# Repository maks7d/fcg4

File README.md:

This project aims to develop an ultra minimalist flight controller for betaflight firmware for FPV drones.
The components are : 
- STM32G473CEU6 (mcu)
- SPL006 (barometer)
- ICM-42688-P (gyro/accel)
No analog OSD and no BlackBox

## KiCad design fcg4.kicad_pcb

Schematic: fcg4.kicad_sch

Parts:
H1: MountingHole; MountingHoles_30.5x30.5mm_Standard

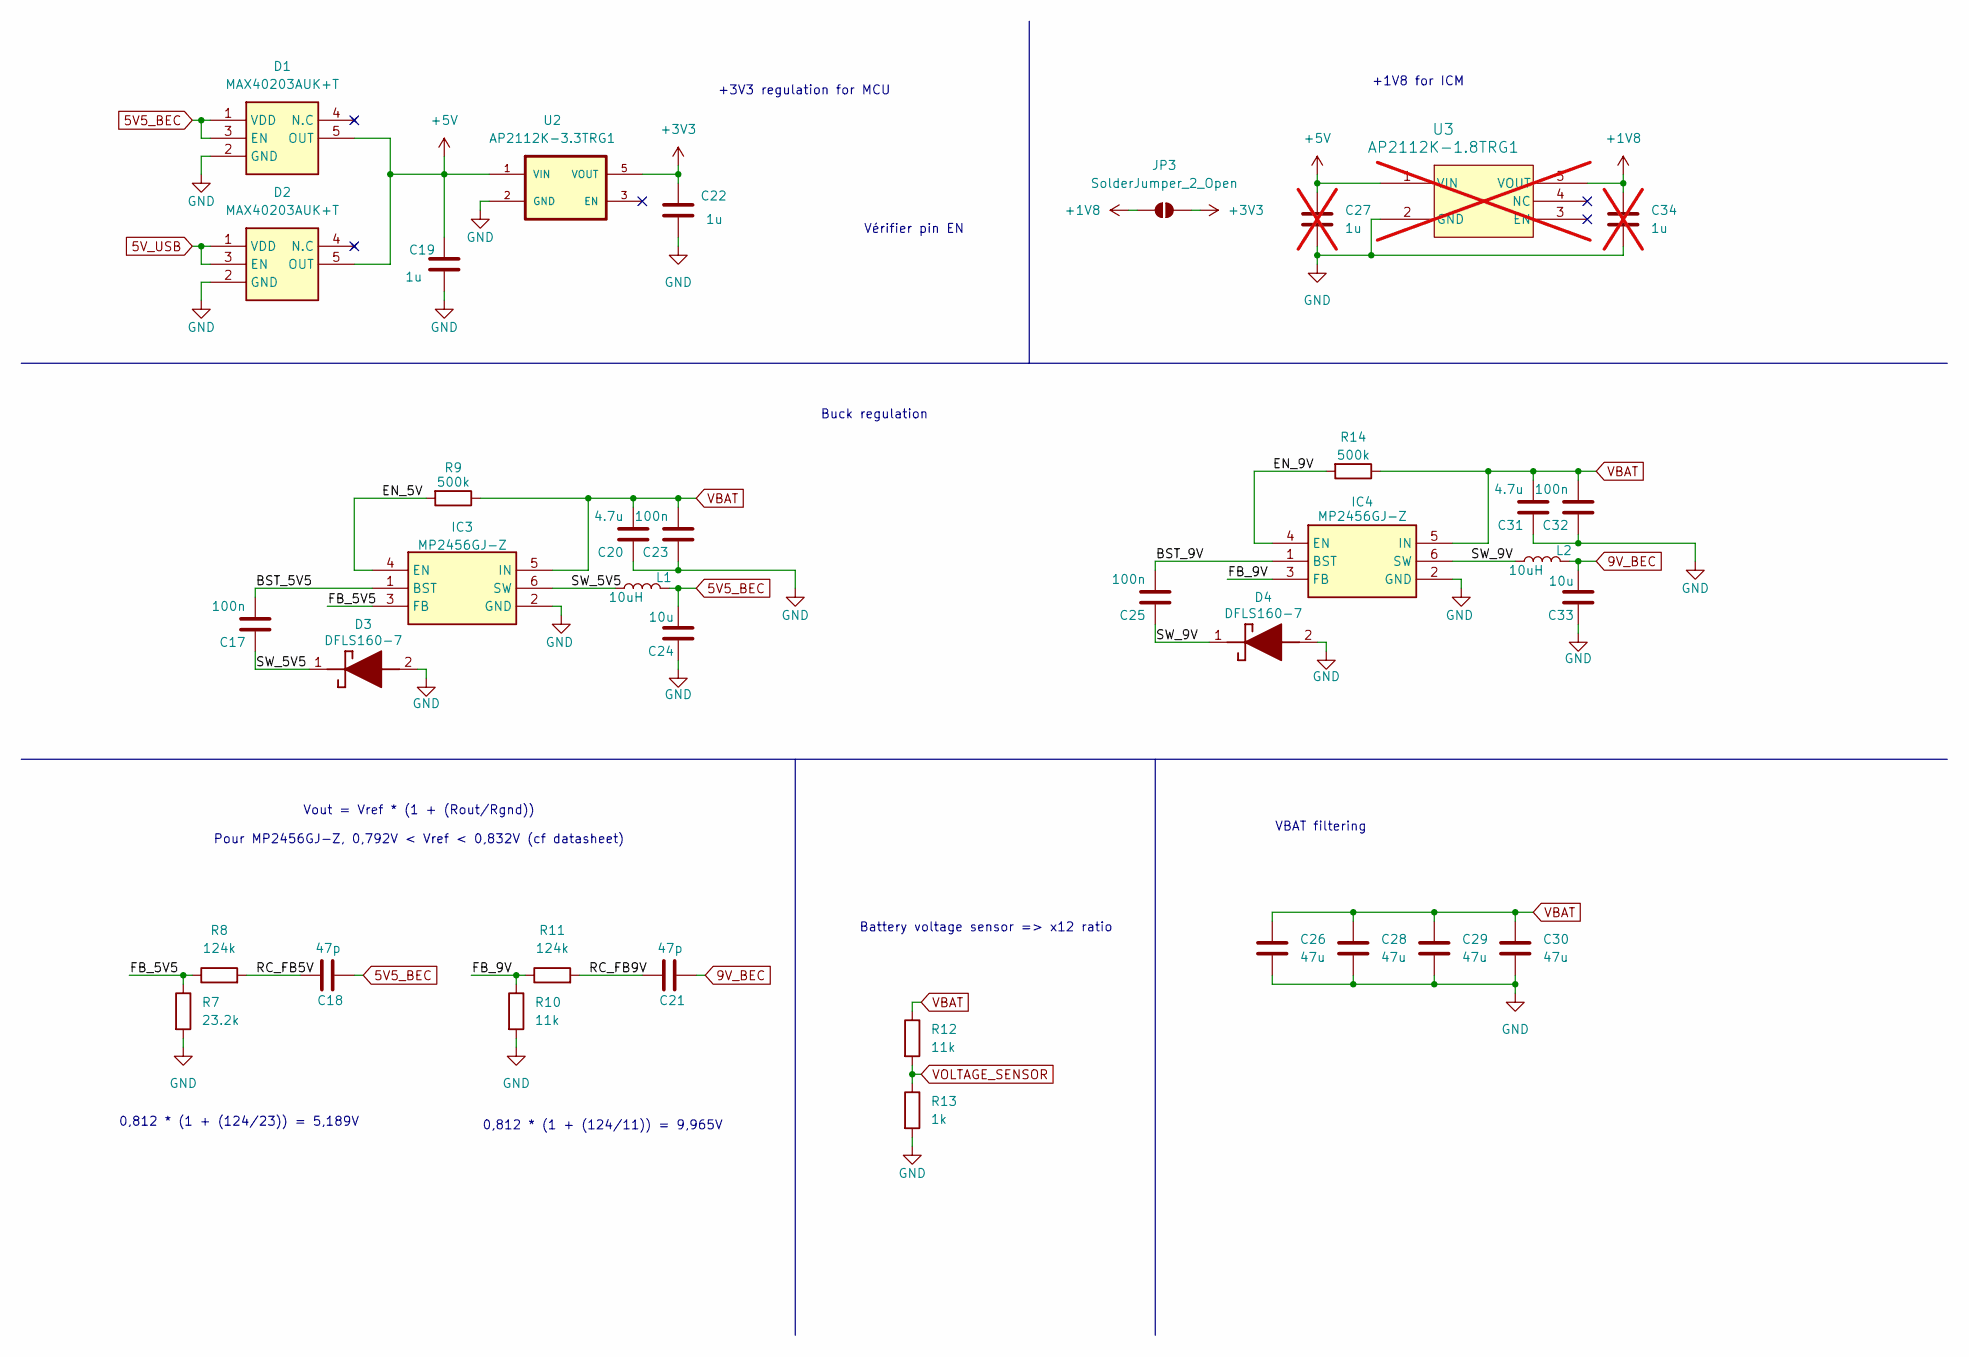
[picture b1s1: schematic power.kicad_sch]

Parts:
C17, C23, C25, C32: 100n; C_0603_1608Metric; Manufacturer_Part_Number CL10B104KB8NNNC; LCSC Part Name C1591
C18, C21: 47p; C_0603_1608Metric; Manufacturer_Part_Number CC0603JRNPO9BN470; LCSC Part Name C105622
C19, C22: 1u; C_0603_1608Metric; Manufacturer_Part_Number CL10B105KB8NQNC; LCSC Part Name C5199872
C20, C31: 4.7u; C_0603_1608Metric; Manufacturer_Part_Number CL10A475KL8NRNC; LCSC Part Name C307467
C24, C33: 10u; C_0603_1608Metric; Manufacturer_Part_Number GRM188R6YA106MA73D; LCSC Part Name C194427
C26, C28, C29, C30: 47u; C_1206_3216Metric; Manufacturer_Part_Number C3216X5R1E476MTJ00E; LCSC Part Name C76659
C27, C34: 1u; C_0603_1608Metric; Manufacturer_Part_Number CL10B105KB8NQNC; LCSC Part Name C5199872; not fitted
D1, D2: MAX40203AUK+T; SOT95P280X145-5M; Mouser Part Number 700-MAX40203AUK+T
D3, D4: DFLS160-7; DFLS1607; Mouser Part Number 621-DFLS160-F
IC3, IC4: MP2456GJ-Z; SOP95P280X100-6M; Mouser Part Number 946-MP2456GJ-Z
JP3: SolderJumper_2_Open; SolderJumper-2_P1.3mm_Open_TrianglePad1.0x1.5mm
L1, L2: 10uH; L_1210_3225Metric; Manufacturer_Part_Number XRTC322512S100MBCA; LCSC Part Name C39846661
R7: 23.2k; R_0603_1608Metric; Manufacturer_Part_Number RT0603BRE0723K2L; LCSC Part Name C861768
R8, R11: 124k; R_0603_1608Metric; Manufacturer_Part_Number 0603WAF1243T5E; LCSC Part Name C22788
R9, R14: 500k; R_0603_1608Metric; Manufacturer_Part_Number 0603WAF4993T5E; LCSC Part Name C26751
R10, R12: 11k; R_0603_1608Metric; Manufacturer_Part_Number 0603WAF1102T5E; LCSC Part Name C25950
R13: 1k; R_0603_1608Metric; Manufacturer_Part_Number RC0603FR-071KL; LCSC Part Name C22548
U2: AP2112K-3.3TRG1; SOT95P285X140-5N; PARTREV 2-2; DigiKey_Part_Number AP2112K-3.3TRG1DICT-ND
U3: AP2112K-1.8TRG1; AP2112K-1.8TRG1_DIO; Manufacturer_Part_Number AP2112K-1.8TRG1; Mouser Part Number 621-AP2112K-1.8TRG1; not fitted

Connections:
5V5_BEC: C18.1, C24.2, D1.1 (VDD), D1.3 (EN), L1.2; also elsewhere on the board
5V_USB: D2.1 (VDD), D2.3 (EN); also elsewhere on the board
9V_BEC: C21.1, C33.2, L2.2; also elsewhere on the board
+1V8: C34.1, JP3.1 (A), U3.5 (VOUT); also elsewhere on the board
+3V3: C22.1, JP3.2 (B), U2.5 (VOUT); also elsewhere on the board
+5V: C19.1, C27.1, D1.5 (OUT), D2.5 (OUT), U2.1 (VIN), U3.1 (VIN); also elsewhere on the board
/Power/BST_5V5: C17.2, IC3.1 (BST)
/Power/BST_9V: C25.2, IC4.1 (BST)
/Power/EN_5V: IC3.4 (EN), R9.2
/Power/EN_9V: IC4.4 (EN), R14.2
/Power/FB_5V5: IC3.3 (FB), R7.1, R8.1
/Power/FB_9V: IC4.3 (FB), R10.1, R11.1
/Power/RC_FB5V: C18.2, R8.2
/Power/RC_FB9V: C21.2, R11.2
/Power/SW_5V5: C17.1, D3.1 (K), IC3.6 (SW), L1.1
/Power/SW_9V: C25.1, D4.1 (K), IC4.6 (SW), L2.1
GND: C19.2, C20.1, C22.2, C23.1, C24.1, C26.2, C27.2, C28.2, C29.2, C30.2, C31.1, C32.1, C33.1, C34.2, D1.2 (GND), D2.2 (GND), D3.2 (A), D4.2 (A), IC3.2 (GND), IC4.2 (GND), R7.2, R10.2, R13.2, U2.2 (GND), U3.2 (GND); also elsewhere on the board
VBAT: C20.2, C23.2, C26.1, C28.1, C29.1, C30.1, C31.2, C32.2, IC3.5 (IN), IC4.5 (IN), R9.1, R12.1, R14.1; also elsewhere on the board
VOLTAGE_SENSOR: R12.2, R13.1; also elsewhere on the board

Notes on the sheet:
+3V3 regulation for MCU
Vérifier pin EN
Vout = Vref * (1 + (Rout/Rgnd)) Pour MP2456GJ-Z, 0,792V < Vref < 0,832V (cf datasheet)
0,812 * (1 + (124/23)) = 5,189V
Battery voltage sensor => x12 ratio
+1V8 for ICM
0,812 * (1 + (124/11)) = 9,965V
VBAT filtering
Buck regulation

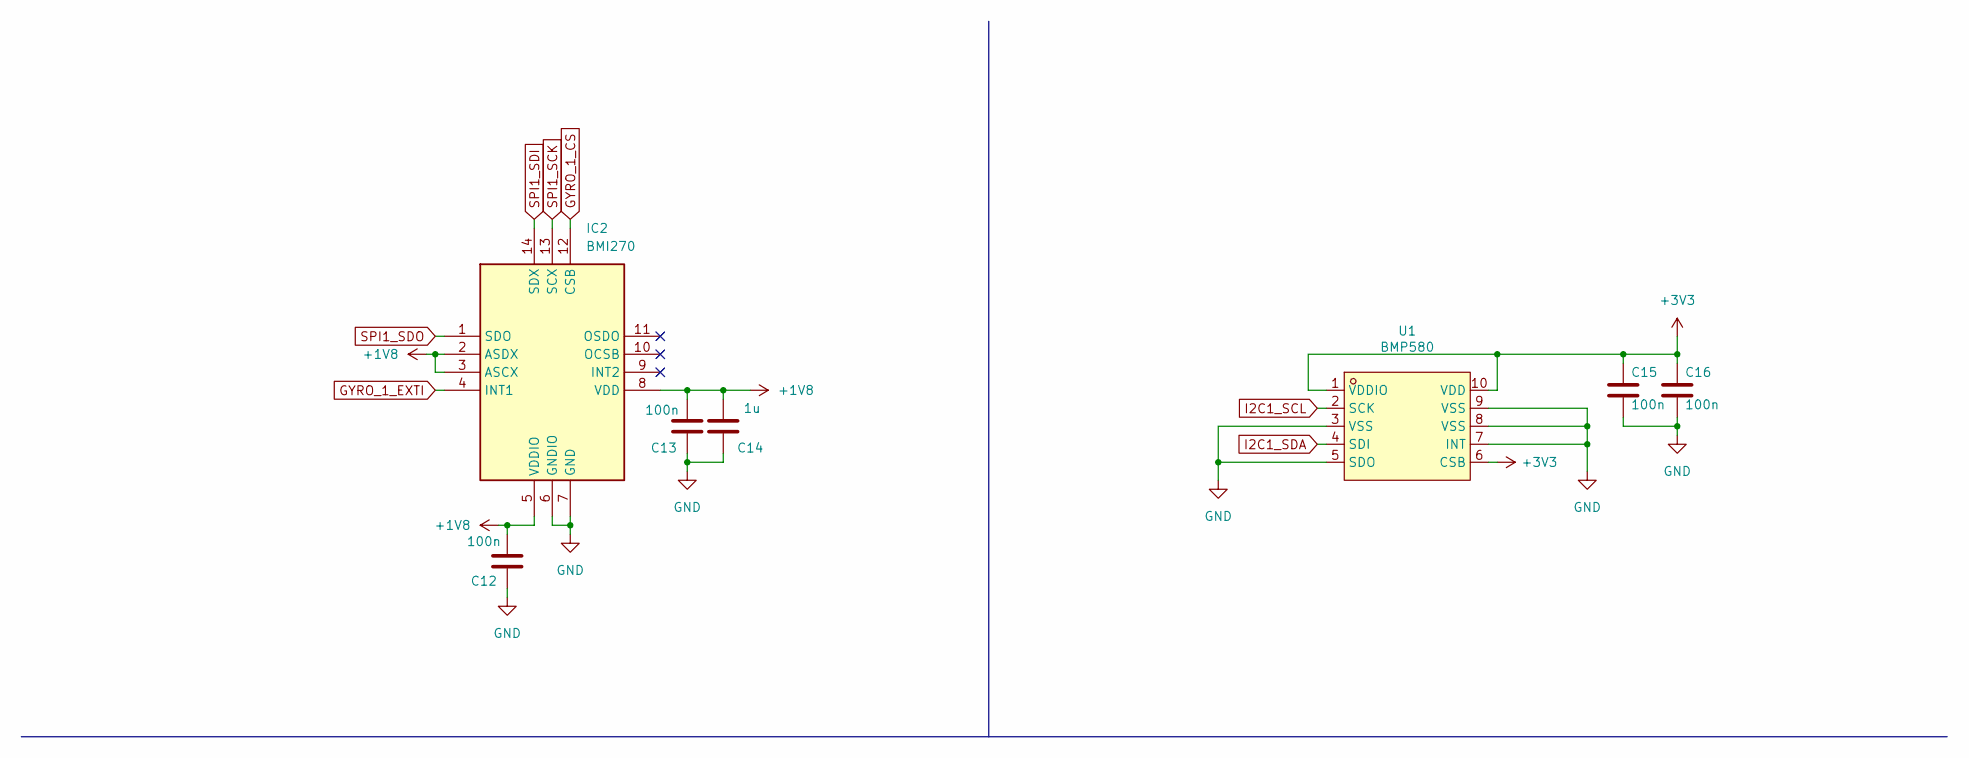
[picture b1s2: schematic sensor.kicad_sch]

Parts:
C12, C13, C15, C16: 100n; C_0603_1608Metric; Manufacturer_Part_Number CL10B104KB8NNNC; LCSC Part Name C1591
C14: 1u; C_0603_1608Metric; Manufacturer_Part_Number CL10B104KB8NNNC; LCSC Part Name C5199872
IC2: BMI270; Mouser Part Number 262-BMI270
U1: BMP580; LGA-10_L2.0-W2.0-P0.50-TL_BMP580; Manufacturer Part BMP580; LCSC Part Name C22391138

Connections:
+1V8: C12.2, C13.2, C14.2, IC2.2 (ASDX), IC2.3 (ASCX), IC2.5 (VDDIO), IC2.8 (VDD); also elsewhere on the board
+3V3: C15.2, C16.2, U1.1 (VDDIO), U1.6 (CSB), U1.10 (VDD); also elsewhere on the board
GND: C12.1, C13.1, C14.1, C15.1, C16.1, IC2.6 (GNDIO), IC2.7 (GND), U1.3 (VSS), U1.5 (SDO), U1.7 (INT), U1.8 (VSS), U1.9 (VSS); also elsewhere on the board
GYRO_1_CS: IC2.12 (CSB); also elsewhere on the board
GYRO_1_EXTI: IC2.4 (INT1); also elsewhere on the board
I2C1_SCL: U1.2 (SCK); also elsewhere on the board
I2C1_SDA: U1.4 (SDI); also elsewhere on the board
SPI1_SCK: IC2.13 (SCX); also elsewhere on the board
SPI1_SDI: IC2.14 (SDX); also elsewhere on the board
SPI1_SDO: IC2.1 (SDO); also elsewhere on the board

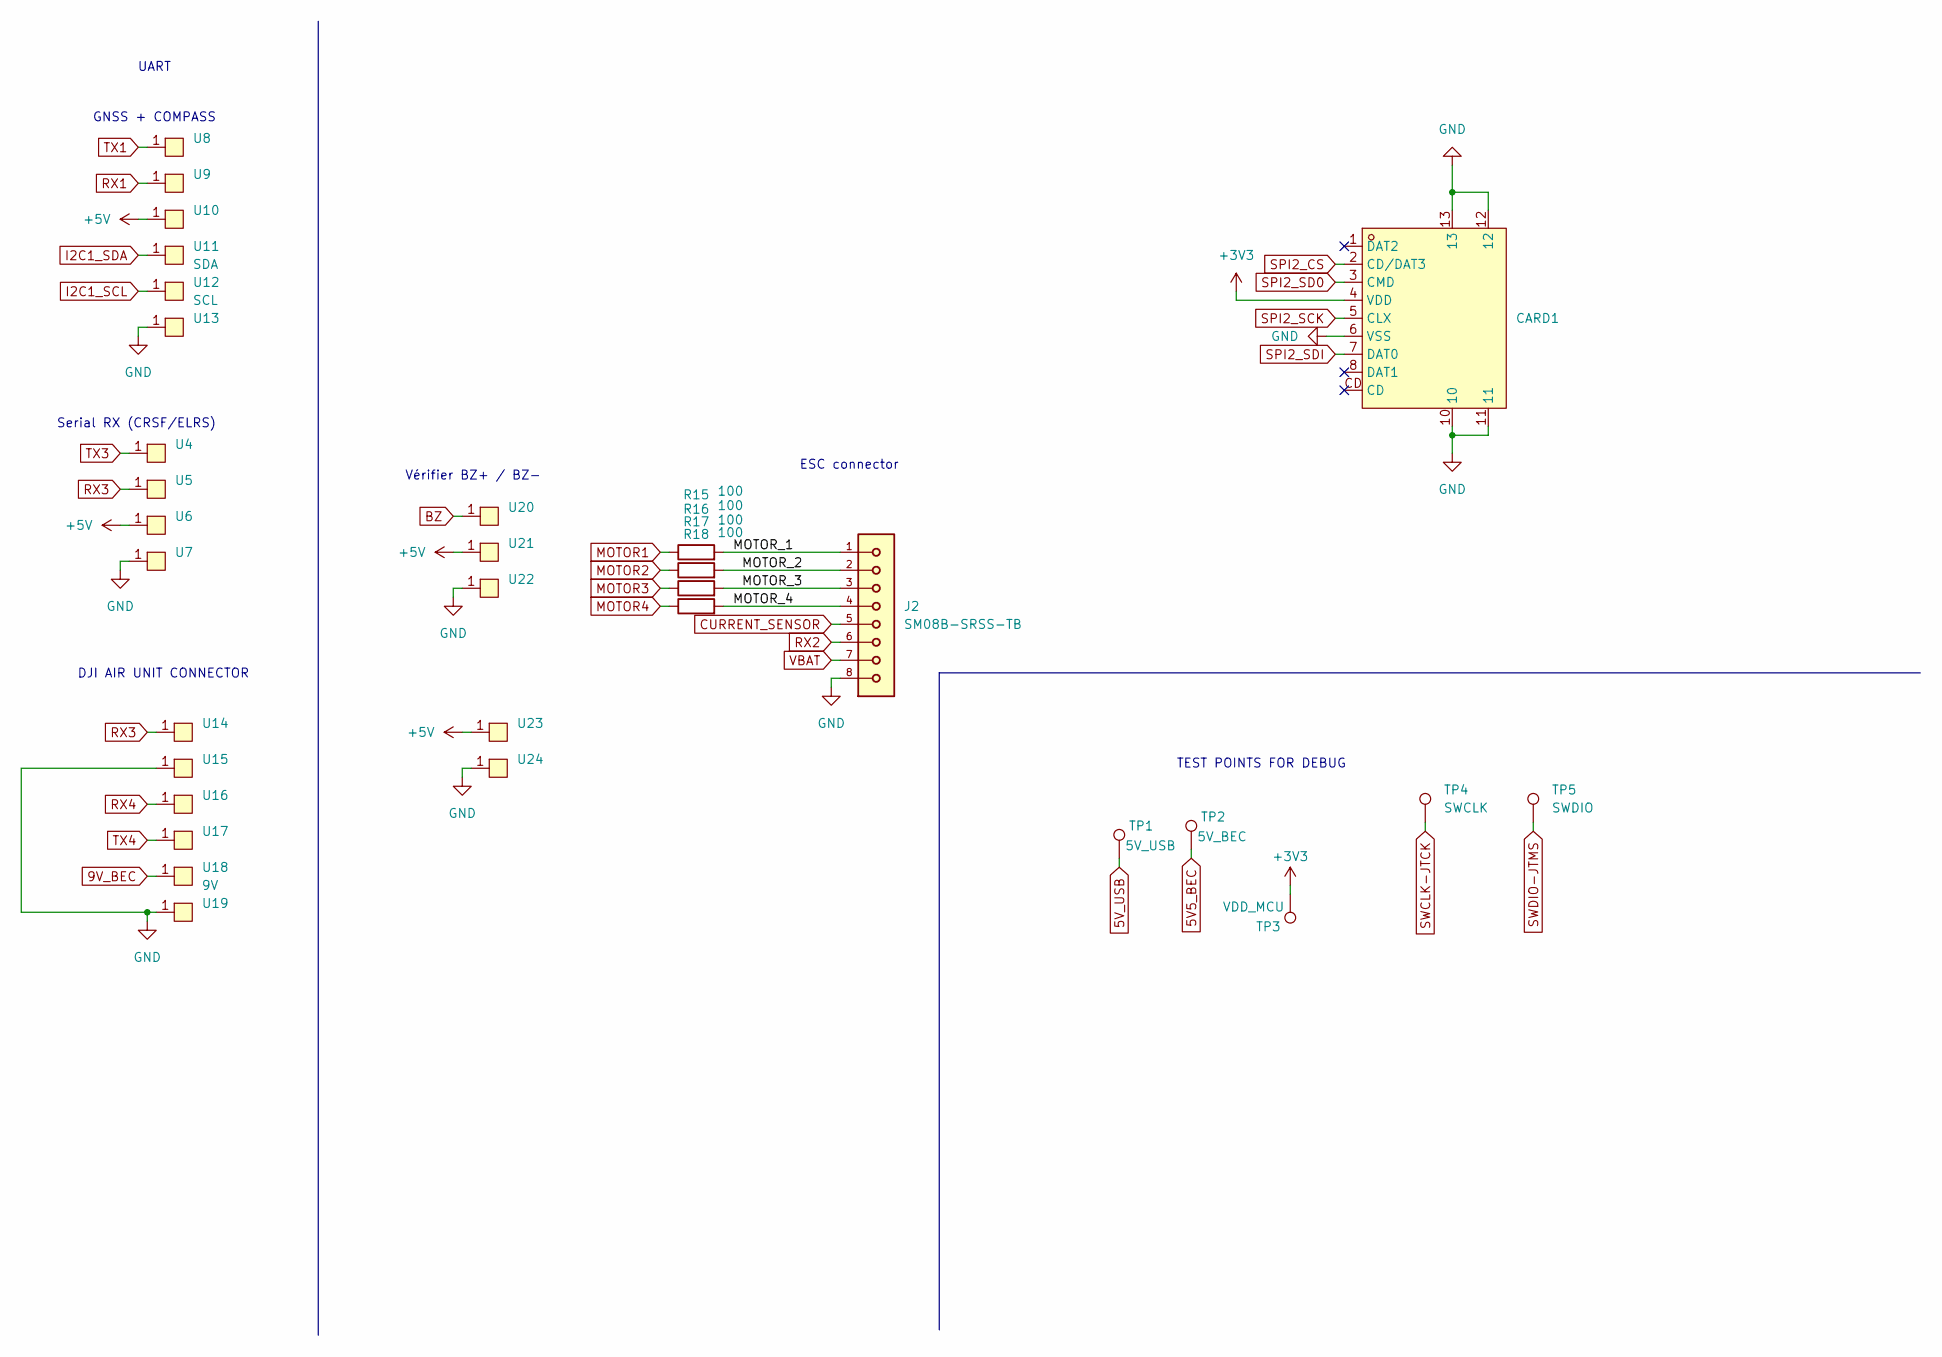
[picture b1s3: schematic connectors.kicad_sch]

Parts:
CARD1: TF-SMD_TF-PUSH; Manufacturer Part TF PUSH; LCSC Part Name 9P，自弹式TF卡座
J2: SM08B-SRSS-TB; JST_SM08B-SRSS-TB; Manufacturer_Part_Number SM08B-SRSS-TB(LF)(SN); DigiKey_Part_Number 455-1808-1-ND
R15, R16, R17, R18: 100; R_0603_1608Metric; Manufacturer_Part_Number FRC0603F5101TS; LCSC Part Name C2907044
TP1: 5V_USB; TestPoint_Pad_D1.0mm
TP2: 5V_BEC; TestPoint_Pad_D1.0mm
TP3: VDD_MCU; TestPoint_Pad_D1.0mm
TP4: SWCLK; TestPoint_Pad_D1.0mm
TP5: SWDIO; TestPoint_Pad_D1.0mm
U4, U5, U6, U7, U8, U9, U10, U13, U14, U15, U16, U17, U19, U20, U21, U22, U23, U24: soldering_pad
U11: SDA; soldering_pad
U12: SCL; soldering_pad
U18: 9V; soldering_pad

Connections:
5V5_BEC: TP2.1 (1_1); also elsewhere on the board
5V_USB: TP1.1 (1_1); also elsewhere on the board
9V_BEC: U18.1; also elsewhere on the board
+3V3: CARD1.4 (VDD), TP3.1 (1_1); also elsewhere on the board
+5V: U6.1, U10.1, U21.1, U23.1; also elsewhere on the board
/Connectors/MOTOR_1: J2.1, R15.2
/Connectors/MOTOR_2: J2.2, R16.2
/Connectors/MOTOR_3: J2.3, R17.2
/Connectors/MOTOR_4: J2.4, R18.2
BZ: U20.1; also elsewhere on the board
CURRENT_SENSOR: J2.5; also elsewhere on the board
GND: CARD1.6 (VSS), CARD1.10, CARD1.11, CARD1.12, CARD1.13, J2.8, U7.1, U13.1, U15.1, U19.1, U22.1, U24.1; also elsewhere on the board
I2C1_SCL: U12.1; also elsewhere on the board
I2C1_SDA: U11.1; also elsewhere on the board
MOTOR1: R15.1; also elsewhere on the board
MOTOR2: R16.1; also elsewhere on the board
MOTOR3: R17.1; also elsewhere on the board
MOTOR4: R18.1; also elsewhere on the board
RX1: U9.1; also elsewhere on the board
RX2: J2.6; also elsewhere on the board
RX3: U5.1, U14.1; also elsewhere on the board
RX4: U16.1; also elsewhere on the board
SPI2_CS: CARD1.2 (CD/DAT3); also elsewhere on the board
SPI2_SCK: CARD1.5 (CLX); also elsewhere on the board
SPI2_SD0: CARD1.3 (CMD); also elsewhere on the board
SPI2_SDI: CARD1.7 (DAT0); also elsewhere on the board
SWCLK-JTCK: TP4.1 (1_1); also elsewhere on the board
SWDIO-JTMS: TP5.1 (1_1); also elsewhere on the board
TX1: U8.1; also elsewhere on the board
TX3: U4.1; also elsewhere on the board
TX4: U17.1; also elsewhere on the board
VBAT: J2.7; also elsewhere on the board

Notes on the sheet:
TEST POINTS FOR DEBUG
UART
GNSS + COMPASS
DJI AIR UNIT CONNECTOR
Vérifier BZ+ / BZ-
Serial RX (CRSF/ELRS)
ESC connector

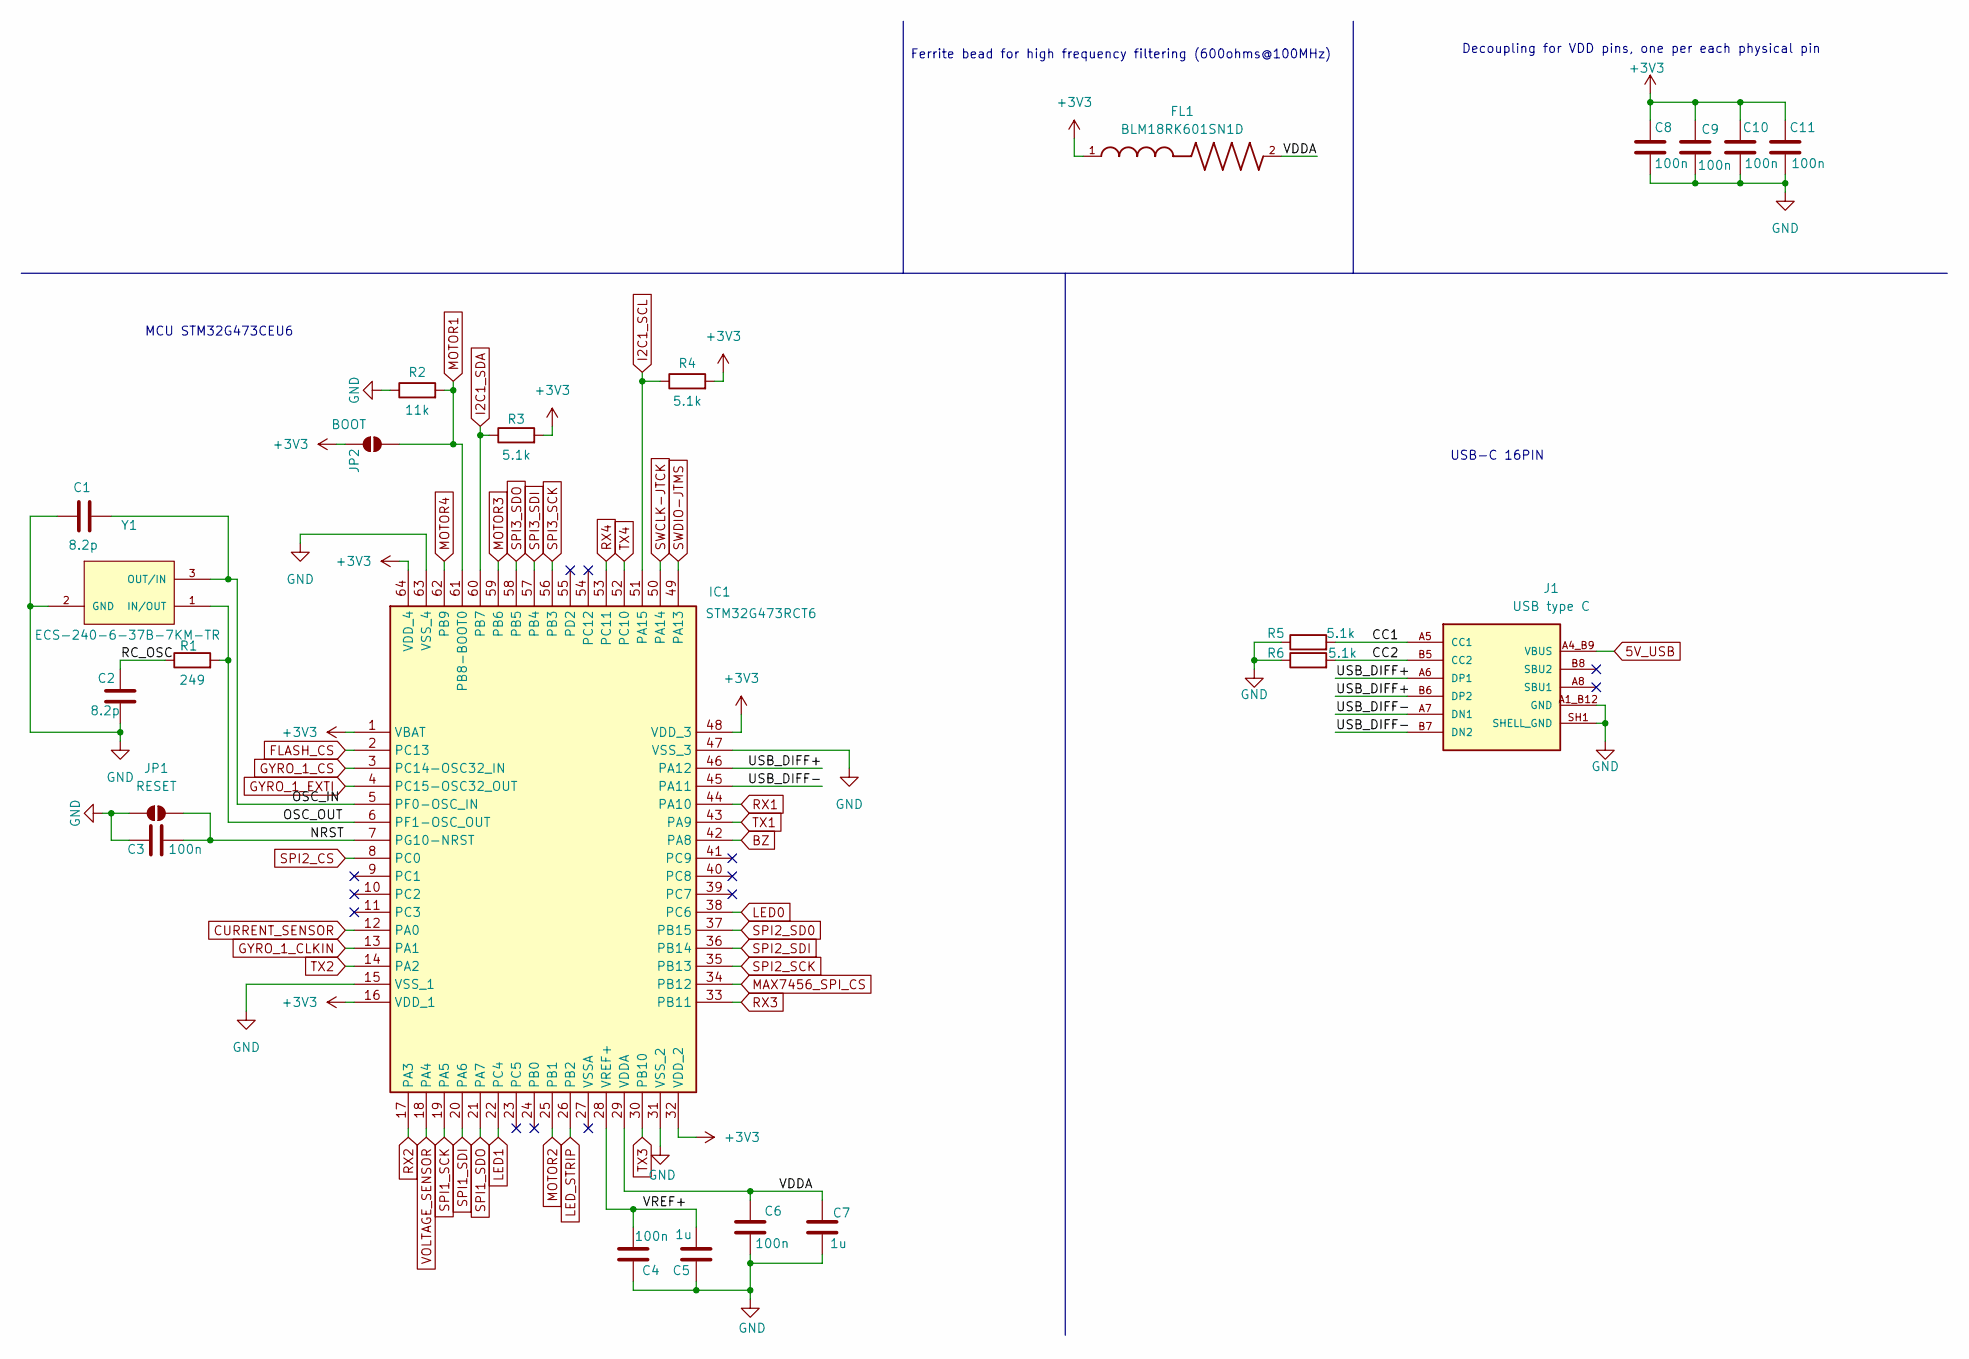
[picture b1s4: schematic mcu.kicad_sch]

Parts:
C1, C2: 8.2p; C_0603_1608Metric; Manufacturer_Part_Number CC0603CRNPO9BN8R2; LCSC Part Name C277519
C3, C4, C6, C8, C9, C10, C11: 100n; C_0603_1608Metric; Manufacturer_Part_Number CL10B104KB8NNNC; LCSC Part Name C1591
C5, C7: 1u; C_0603_1608Metric; Manufacturer_Part_Number CL10B105KB8NQNC; LCSC Part Name C5199872
FL1: BLM18RK601SN1D; BEADC1608X95N; Manufacturer_Part_Number BLM18RK601SN1D; DigiKey_Part_Number 490-5227-1-ND
IC1: STM32G473RCT6; QFP50P1200X1200X160-64M; Mouser Part Number 511-STM32G473RCT6
J1: USB type C; GCT_USB4105-GF-A-120; PARTREV B3; DigiKey_Part_Number 2073-USB4105-GF-A-120CT-ND
JP1: RESET; SolderJumper-2_P1.3mm_Open_RoundedPad1.0x1.5mm
JP2: BOOT; SolderJumper-2_P1.3mm_Open_RoundedPad1.0x1.5mm
R1: 249; R_0603_1608Metric; Manufacturer_Part_Number FRC0603F2490TS; LCSC Part Name C2933176
R2: 11k; R_0603_1608Metric; Manufacturer_Part_Number 0603WAF1102T5E; LCSC Part Name C25950
R3, R4, R5, R6: 5.1k; R_0603_1608Metric; Manufacturer_Part_Number FRC0603F5101TS; LCSC Part Name C2907044
Y1: ECS-240-6-37B-7KM-TR; XTAL_ECS-240-6-37B-7KM-TR; Manufacturer_Part_Number ECS-240-6-37B-7KM-TR; DigiKey_Part_Number 50-ECS-240-6-37B-7KM-CT-ND

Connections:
5V_USB: J1.A4_B9 (VBUS); also elsewhere on the board
+3V3: C8.1, C9.1, C10.1, C11.1, FL1.1, IC1.1 (VBAT), IC1.16 (VDD_1), IC1.32 (VDD_2), IC1.48 (VDD_3), IC1.64 (VDD_4), JP2.1 (A), R3.2, R4.2; also elsewhere on the board
/MCU/CC1: J1.A5 (CC1), R5.2
/MCU/CC2: J1.B5 (CC2), R6.2
/MCU/NRST: C3.2, IC1.7 (PG10-NRST), JP1.2 (B)
/MCU/OSC_IN: C1.2, IC1.5 (PF0-OSC_IN), Y1.3 (OUT/IN)
/MCU/OSC_OUT: IC1.6 (PF1-OSC_OUT), R1.2, Y1.1 (IN/OUT)
/MCU/RC_OSC: C2.1, R1.1
/MCU/USB_DIFF+: IC1.46 (PA12), J1.A6 (DP1), J1.B6 (DP2)
/MCU/USB_DIFF-: IC1.45 (PA11), J1.A7 (DN1), J1.B7 (DN2)
/MCU/VDDA: C6.2, C7.2, FL1.2, IC1.29 (VDDA)
/MCU/VREF+: C4.2, C5.2, IC1.28 (VREF+)
BZ: IC1.42 (PA8); also elsewhere on the board
CURRENT_SENSOR: IC1.12 (PA0); also elsewhere on the board
FLASH_CS: IC1.2 (PC13)
GND: C1.1, C2.2, C3.1, C4.1, C5.1, C6.1, C7.1, C8.2, C9.2, C10.2, C11.2, IC1.15 (VSS_1), IC1.31 (VSS_2), IC1.47 (VSS_3), IC1.63 (VSS_4), J1.A1_B12 (GND), J1.SH1 (SHELL_GND), JP1.1 (A), R2.1, R5.1, R6.1, Y1.2 (GND); also elsewhere on the board
GYRO_1_CLKIN: IC1.13 (PA1)
GYRO_1_CS: IC1.3 (PC14-OSC32_IN); also elsewhere on the board
GYRO_1_EXTI: IC1.4 (PC15-OSC32_OUT); also elsewhere on the board
I2C1_SCL: IC1.51 (PA15), R4.1; also elsewhere on the board
I2C1_SDA: IC1.60 (PB7), R3.1; also elsewhere on the board
LED0: IC1.38 (PC6)
LED1: IC1.22 (PC4)
LED_STRIP: IC1.26 (PB2)
MAX7456_SPI_CS: IC1.34 (PB12)
MOTOR1: IC1.61 (PB8-BOOT0), JP2.2 (B), R2.2; also elsewhere on the board
MOTOR2: IC1.25 (PB1); also elsewhere on the board
MOTOR3: IC1.59 (PB6); also elsewhere on the board
MOTOR4: IC1.62 (PB9); also elsewhere on the board
RX1: IC1.44 (PA10); also elsewhere on the board
RX2: IC1.17 (PA3); also elsewhere on the board
RX3: IC1.33 (PB11); also elsewhere on the board
RX4: IC1.53 (PC11); also elsewhere on the board
SPI1_SCK: IC1.19 (PA5); also elsewhere on the board
SPI1_SDI: IC1.20 (PA6); also elsewhere on the board
SPI1_SDO: IC1.21 (PA7); also elsewhere on the board
SPI2_CS: IC1.8 (PC0); also elsewhere on the board
SPI2_SCK: IC1.35 (PB13); also elsewhere on the board
SPI2_SD0: IC1.37 (PB15); also elsewhere on the board
SPI2_SDI: IC1.36 (PB14); also elsewhere on the board
SPI3_SCK: IC1.56 (PB3)
SPI3_SDI: IC1.57 (PB4)
SPI3_SDO: IC1.58 (PB5)
SWCLK-JTCK: IC1.50 (PA14); also elsewhere on the board
SWDIO-JTMS: IC1.49 (PA13); also elsewhere on the board
TX1: IC1.43 (PA9); also elsewhere on the board
TX2: IC1.14 (PA2)
TX3: IC1.30 (PB10); also elsewhere on the board
TX4: IC1.52 (PC10); also elsewhere on the board
VOLTAGE_SENSOR: IC1.18 (PA4); also elsewhere on the board

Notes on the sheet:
USB-C 16PIN
Ferrite bead for high frequency filtering (600ohms@100MHz)
Decoupling for VDD pins, one per each physical pin
MCU STM32G473CEU6

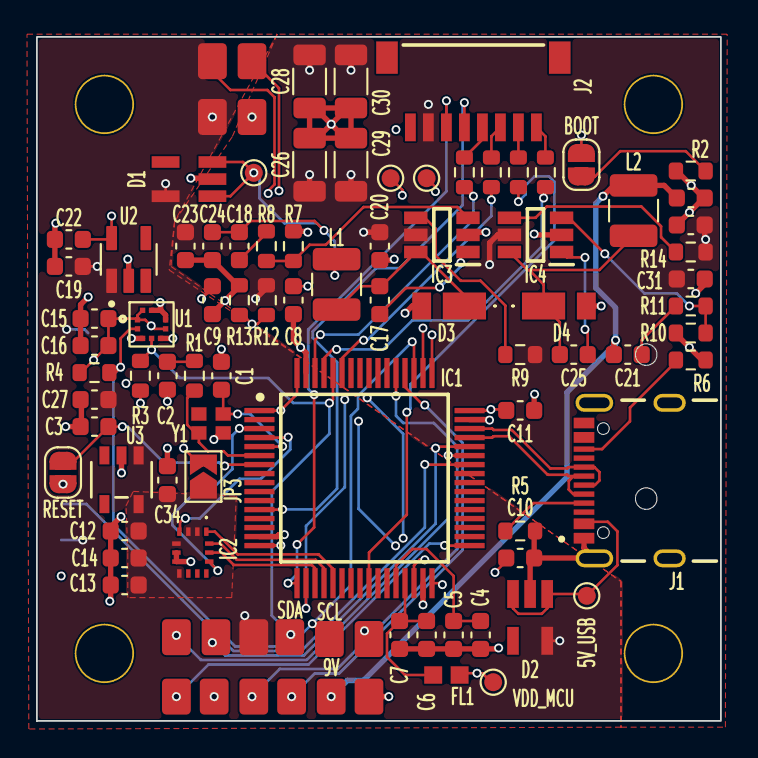
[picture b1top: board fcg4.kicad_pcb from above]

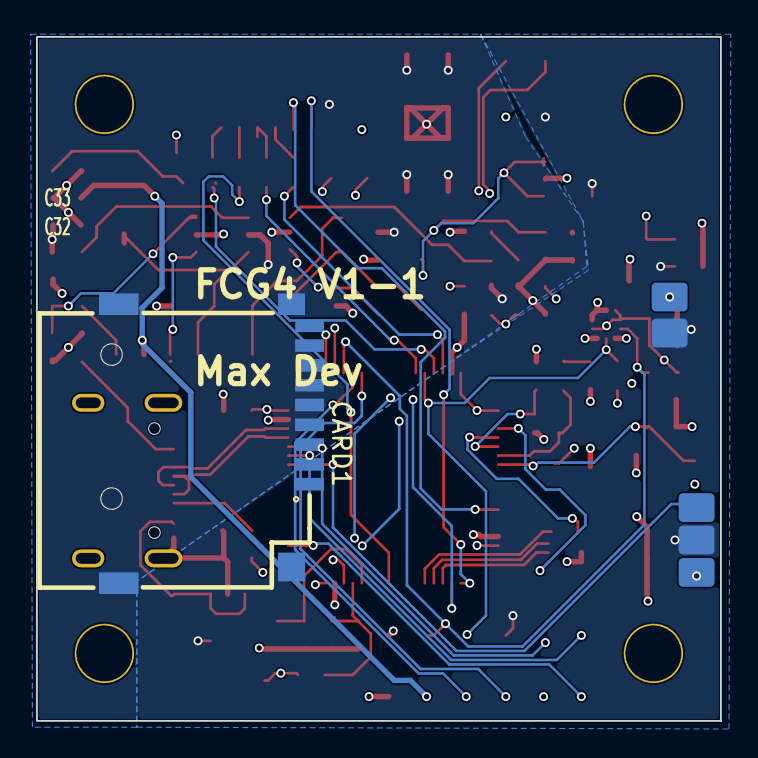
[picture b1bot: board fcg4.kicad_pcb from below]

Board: 4 copper layers, 38.0 x 38.0 mm, 100 parts (6 on the bottom side), 59 nets.

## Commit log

2026-02-11 init
2026-02-11 add readme
2026-02-12 add first few components
2026-02-12 first components on schematic and few wiring
2026-02-12 Remove lock file for mcu schematic to prevent conflicts during editing
2026-02-13 Refactor sensor.kicad_sch: Adjust component positions and update property attributes for ICM-42688-P
2026-02-13 Refactor code structure for improved readability and maintainability
2026-02-14 add sensors schematic
2026-02-14 removed DS store from git cache
2026-02-14 finished buck schematic and designed solder pads footprints
2026-02-15 add wiring to soldering pads for uart, dji, and esc
2026-02-15 - Removed SBUS receiver support in uart1 and added esc telemetry in uart2 - Added a new Mounting Hole symbol with properties and graphical representation in the schematic (fcg4.kicad_sch). (MountingH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
2026-02-15 - affected footprints for components - started placing components
2026-02-16 Placed every components on one face only
2026-02-17 Started routing
2026-02-18 removed schottky diodes to use ideal diodes smaller
2026-02-18 add 100ohm for pwm and some routing
2026-02-18 add additional wire connections and update MOTOR labels in schematic
2026-02-18 routing...
2026-02-20 routing
2026-02-20 Update board settings and design rules in KiCad project files
    - Changed active layer from 0 to 2 and disabled auto track width in fcg4.kicad_prl.
    - Adjusted column widths for better layout in fcg4.kicad_prl.
    - Increased silk text size and thickness for improved visibility in fcg4.kicad_pro.
    - Changed track and via dangling rules from warning to error for stricter design checks in fcg4.kicad_pro.
    - Updated minimum hole-to-hole clearance and via annular width for enhanced manufacturability in fcg4.kicad_pro.
2026-02-21 Update footprint references and component values in schematic files
    - Changed footprint property for a component in mcu.kicad_sch from "Package_DFN_QFN:QFN-48-1EP_7x7mm_P0.5mm_EP5.6x5.6mm" to "fcg4_fp:QFN-48-1EP_7x7mm_P0.5mm_EP5.6x5.6mm".
    - Updated value property for a component in mcu.kicad_sch from "SolderJumper_2_Open" to "BOOT".
    - Changed value property for another component in mcu.kicad_sch from "SolderJumper_2_Open" to "RESET".
    - Modified footprint property for a component in sensor.kicad_sch from "ProLib_pcs_2026-02-12:SENSOR-SMD_SPL06-001" to "fcg4_fp:SENSOR-SMD_SPL06-001".
2026-02-21 update routing and pcb cuts edge
2026-02-21 Add new Gerber job file for fcg4 project with complete specifications and material stackup
2026-02-21 Update KiCad project files and component specifications
    - Modified visible layers in fcg4.kicad_prl to adjust layer visibility settings.
    - Increased via diameter and drill size in fcg4.kicad_pro for improved connectivity.
    - Adjusted soldering pad dimensions in soldering_pad.kicad_mod for better fit.
    - Updated fp-info-cache with new identifier for BatteryClip_Keystone_54_D16-19mm.
2026-02-22 Update component properties in schematics with manufacturer details and datasheets
    - Added manufacturer name, part number, and LCSC part name for various components in mcu.kicad_sch, power.kicad_sch, and sensor.kicad_sch.
    - Updated datasheet links for components to point to the correct URLs.
    - Ensured all new properties are hidden in the schematic view.
2026-02-23 update edges
2026-02-24 Almost completed! Update component properties in sensor schematic
    - Added datasheets, LCSC part names, manufacturer names, and manufacturer part numbers for various components in the sensor.kicad_sch file.
    - Updated the datasheet links for components to point to the correct URLs.
2026-02-25 PCB v1 ready for manufacturing all the CAM files are available in CAM folder
2026-02-25 Add Availability and Price properties to multiple components in schematic
2026-02-27 update buck regulator to a more recent one
2026-02-28 finished re routing with new buck regulators
2026-03-20 switch stm323g473ceu6 to stm32g473cet6 for easier soldering package
2026-03-23 reorganized everything and switched to 0603 as a minimum size
2026-04-01 update routing
2026-04-10 update silkscreen
2026-04-11 changed barometer to BMP580 and completed BOM
2026-04-12 switch IMU to BMI270
2026-05-31 add microsd card connector
